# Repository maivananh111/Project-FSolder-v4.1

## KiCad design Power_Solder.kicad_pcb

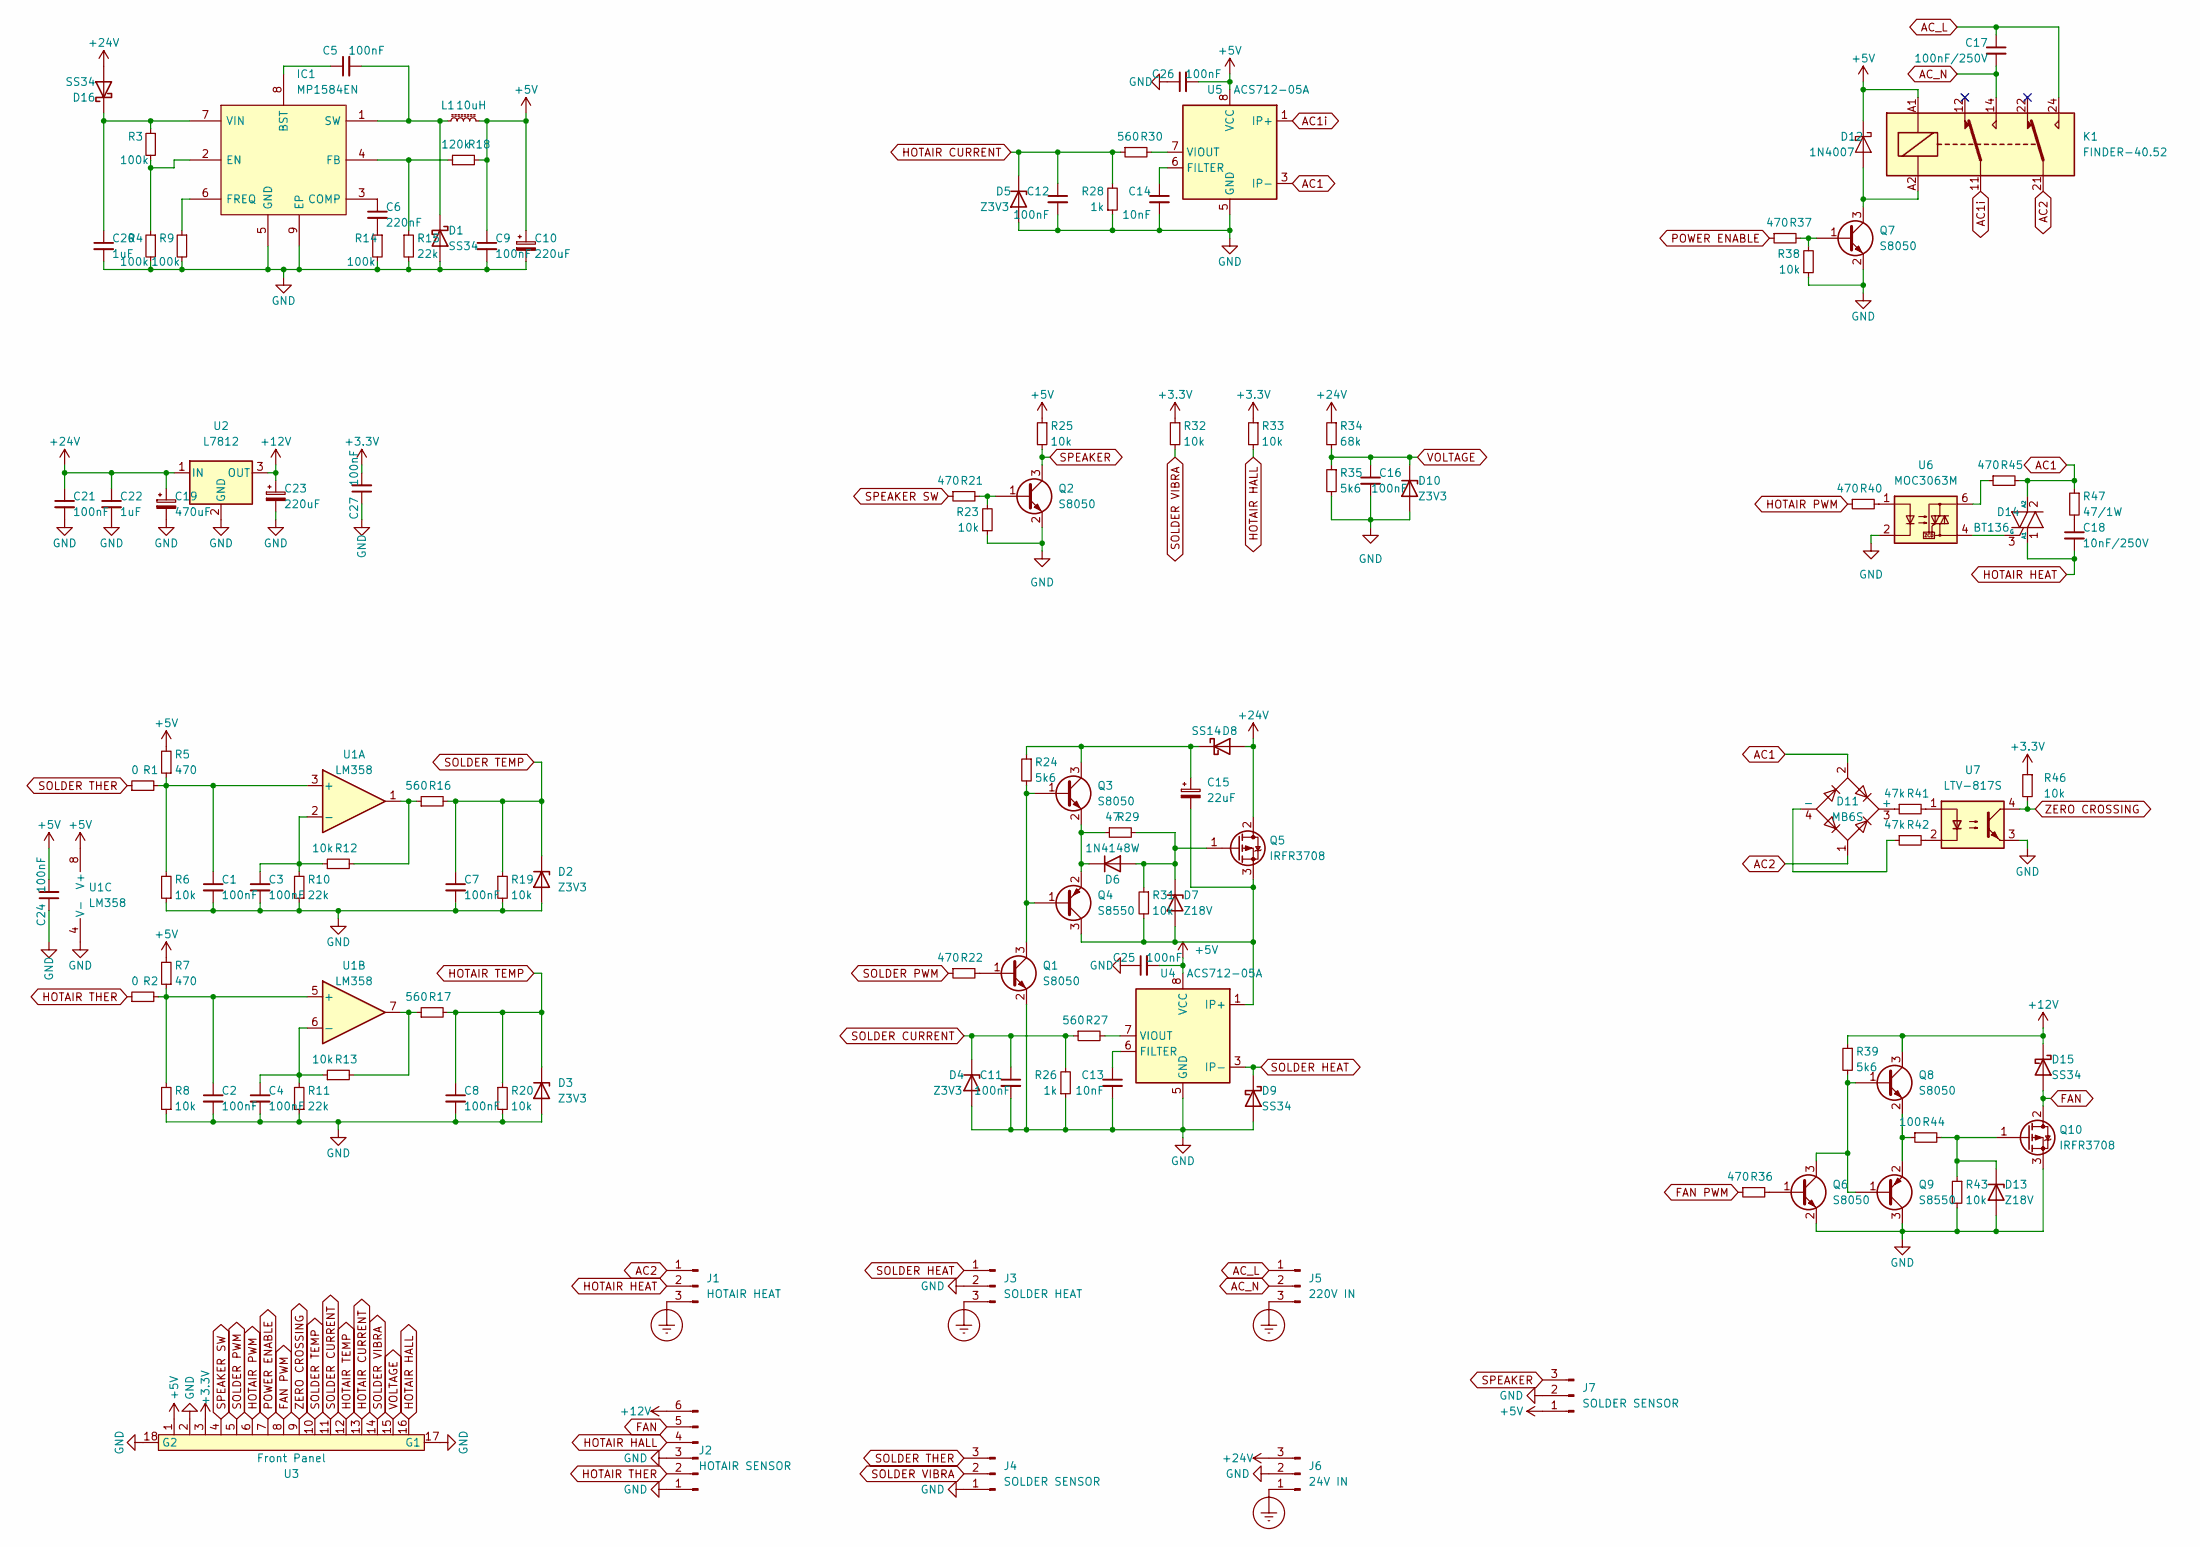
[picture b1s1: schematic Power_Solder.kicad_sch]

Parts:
C1, C2, C3, C4, C5, C7, C8, C9, C11, C12, C16, C21, C24, C25, C26, C27: 100nF; C_0603_1608Metric
C6: 220nF; C_0603_1608Metric
C10, C23: 220uF; CP_Elec_6.3x7.7
C13, C14: 10nF; C_0603_1608Metric
C15: 22uF; CP_EIA-6032-20_AVX-F
C17: 100nF/250V; C_Rect_L13.0mm_W5.0mm_P10.00mm_FKS3_FKP3_MKS4
C18: 10nF/250V; C_1206_3216Metric
C19: 470uF; CP_Elec_10x10.5
C20, C22: 1uF; C_0603_1608Metric
D1, D9, D15, D16: SS34; D_SMA
D2, D3, D4, D5, D10: Z3V3; D_MiniMELF
D6: 1N4148W; D_SOD-123
D7, D13: Z18V; D_MiniMELF
D8: SS14; D_SMA
D11: MB6S; TO-269AA
D12: 1N4007; D_SOD-123F
D14: BT136; TO-252-2
IC1: MP1584EN; SOIC-8-1EP_3.9x4.9mm_P1.27mm_EP2.514x3.2mm
J1: HOTAIR HEAT; JST_VH_B3P-VH-B_1x03_P3.96mm_Vertical
J2: HOTAIR SENSOR; XH_6P_2.54mm_Vertical
J3: SOLDER HEAT; JST_VH_B3P-VH-B_1x03_P3.96mm_Vertical
J4, J7: SOLDER SENSOR; XH_3P_2.54mm_Vertical
J5: 220V IN; JST_VH_B3P-VH-B_1x03_P3.96mm_Vertical
J6: 24V IN; JST_VH_B3P-VH-B_1x03_P3.96mm_Vertical
K1: FINDER-40.52; Relay_DPDT_Finder_40.52
L1: 10uH; L_Abracon_ASPI-0630LR
Q1, Q2, Q3, Q6, Q7, Q8: S8050; SOT-23
Q4, Q9: S8550; SOT-23
Q5, Q10: IRFR3708; TO-252-2
R1, R2: 0; R_0603_1608Metric
R3, R4, R9, R14: 100k; R_0603_1608Metric
R5, R7, R21, R22, R36, R37, R40, R45: 470; R_0603_1608Metric
R6, R8, R12, R13, R19, R20, R23, R25, R31, R32, R33, R38, R43, R46: 10k; R_0603_1608Metric
R10, R11, R15: 22k; R_0603_1608Metric
R16, R17, R27, R30: 560; R_0603_1608Metric
R18: 120k; R_0603_1608Metric
R24, R35, R39: 5k6; R_0603_1608Metric
R26, R28: 1k; R_0603_1608Metric
R29: 47; R_0603_1608Metric
R34: 68k; R_0603_1608Metric
R41, R42: 47k; R_0603_1608Metric
R44: 100; R_0603_1608Metric
R47: 47/1W; R_1206_3216Metric
U1: LM358; SOIC-8_3.9x4.9mm_P1.27mm
U2: L7812; TO-263-3_TabPin2
U3: Front Panel; FPC_16P_1mm
U4, U5: ACS712-05A; SOIC-8_3.9x4.9mm_P1.27mm
U6: MOC3063M; DIP-6_W7.62mm_LongPads
U7: LTV-817S; SMDIP-4_W9.53mm

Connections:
+3.3V: C27.2, R32.1, R33.1, R46.1, U3.3
+5V: C9.1, C10.1, C24.2, C25.2, C26.2, D12.1 (K), J7.1, K1.A1, L1.2, R5.2, R7.2, R18.2, R25.1, U1.8 (V+), U3.1, U4.8 (VCC), U5.8 (VCC)
+12V: C23.1, D15.1 (K), J2.6, Q8.3 (C), R39.1, U2.3 (OUT)
+24V: C19.1, C21.1, C22.1, D8.2 (A), D16.2 (A), J6.3, Q5.2 (D), R34.1, U2.1 (IN)
AC1: D11.2, D14.2 (A2), R45.2, R47.1, U5.3 (IP-), U5.4 (IP-)
AC1i: K1.11, U5.1 (IP+), U5.2 (IP+)
AC2: D11.1, J1.1, K1.21
AC_L: C17.1, J5.1, K1.24
AC_N: C17.2, J5.2, K1.14
Earth_Protective: J1.3, J3.3, J5.3, J6.1
FAN: D15.2 (A), J2.5, Q10.2 (D)
FAN PWM: R36.1, U3.8
GND: C1.2, C2.2, C3.2, C4.2, C7.2, C8.2, C9.2, C10.2, C11.2, C12.2, C13.2, C14.2, C16.2, C19.2, C20.2, C21.2, C22.2, C23.2, C24.1, C25.1, C26.1, C27.1, D1.2 (A), D2.2 (A), D3.2 (A), D4.2 (A), D5.2 (A), D9.2 (A), D10.2 (A), D13.2 (A), IC1.5 (GND), IC1.9 (EP), J2.1, J2.3, J3.2, J4.1, J6.2, J7.2, Q1.2 (E), Q2.2 (E), Q6.2 (E), Q7.2 (E), Q9.3 (C), Q10.3 (S), R4.2, R6.1, R8.1, R9.2, R10.1, R11.1, R14.2, R15.2, R19.2, R20.2, R23.1, R26.1, R28.1, R35.2, R38.1, R43.2, U1.4 (V-), U2.2 (GND), U3.2, U3.17 (G1), U3.18 (G2), U4.5 (GND), U5.5 (GND), U6.2, U7.3
HOTAIR CURRENT: C12.1, D5.1 (K), R28.2, R30.1, U3.13
HOTAIR HALL: J2.4, R33.2, U3.16
HOTAIR HEAT: C18.2, D14.1 (A1), J1.2
HOTAIR PWM: R40.1, U3.6
HOTAIR TEMP: C8.1, D3.1 (K), R17.2, R20.1, U3.12
HOTAIR THER: J2.2, R2.1
unnamed: C6.2, R14.1
unnamed: C18.1, R47.2
unnamed: C5.2, D1.1 (K), IC1.1 (SW), L1.1
unnamed: D6.2 (A), D7.1 (K), Q5.1 (G), R29.2, R31.1
unnamed: D6.1 (K), Q3.2 (E), Q4.2 (E), R29.1
unnamed: C15.2, D7.2 (A), Q4.3 (C), Q5.3 (S), R31.2, U4.1 (IP+), U4.2 (IP+)
unnamed: C15.1, D8.1 (K), Q3.3 (C), R24.1
unnamed: D11.3 (+), R41.1
unnamed: D11.4 (-), R42.1
unnamed: D12.2 (A), K1.A2, Q7.3 (C)
unnamed: D13.1 (K), Q10.1 (G), R43.1, R44.2
unnamed: D14.3 (G), U6.4
unnamed: C20.1, D16.1 (K), IC1.7 (VIN), R3.1
unnamed: C5.1, IC1.8 (BST)
unnamed: C6.1, IC1.3 (COMP)
unnamed: IC1.2 (EN), R3.2, R4.1
unnamed: IC1.4 (FB), R15.1, R18.1
unnamed: IC1.6 (FREQ), R9.1
unnamed: Q1.1 (B), R22.2
unnamed: Q1.3 (C), Q3.1 (B), Q4.1 (B), R24.2
unnamed: Q2.1 (B), R21.2, R23.2
unnamed: Q6.1 (B), R36.2
unnamed: Q6.3 (C), Q8.1 (B), Q9.1 (B), R39.2
unnamed: Q7.1 (B), R37.2, R38.2
unnamed: Q8.2 (E), Q9.2 (E), R44.1
unnamed: R12.2, R16.1, U1.1
unnamed: R13.2, R17.1, U1.7
unnamed: R40.2, U6.1
unnamed: R41.2, U7.1
unnamed: R42.2, U7.2
unnamed: R45.1, U6.6
unnamed: C1.1, R1.2, R5.1, R6.2, U1.3 (+)
unnamed: C3.1, R10.2, R12.1, U1.2 (-)
unnamed: C2.1, R2.2, R7.1, R8.2, U1.5 (+)
unnamed: C4.1, R11.2, R13.1, U1.6 (-)
unnamed: C13.1, U4.6 (FILTER)
unnamed: R27.2, U4.7 (VIOUT)
unnamed: C14.1, U5.6 (FILTER)
unnamed: R30.2, U5.7 (VIOUT)
POWER ENABLE: R37.1, U3.7
SOLDER CURRENT: C11.1, D4.1 (K), R26.2, R27.1, U3.11
SOLDER HEAT: D9.1 (K), J3.1, U4.3 (IP-), U4.4 (IP-)
SOLDER PWM: R22.1, U3.5
SOLDER TEMP: C7.1, D2.1 (K), R16.2, R19.1, U3.10
SOLDER THER: J4.3, R1.1
SOLDER VIBRA: J4.2, R32.2, U3.14
SPEAKER: J7.3, Q2.3 (C), R25.2
SPEAKER SW: R21.1, U3.4
VOLTAGE: C16.1, D10.1 (K), R34.2, R35.1, U3.15
ZERO CROSSING: R46.2, U3.9, U7.4

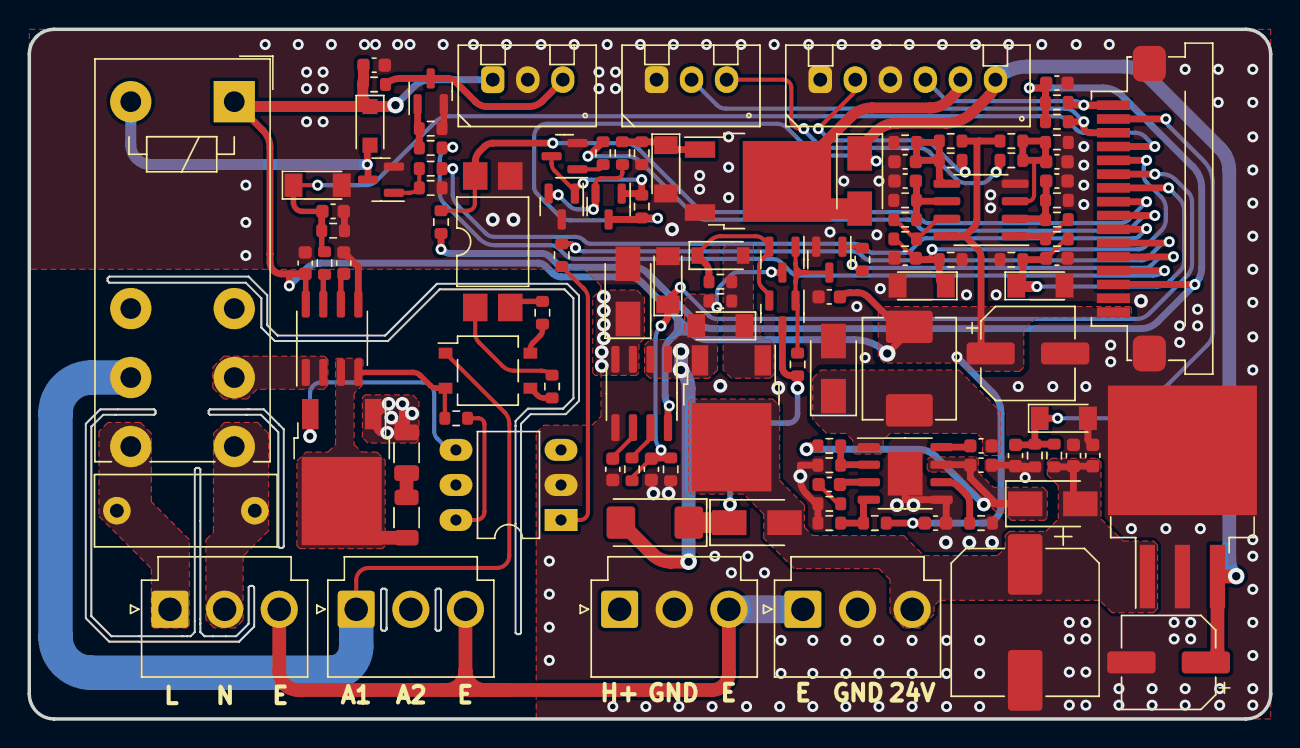
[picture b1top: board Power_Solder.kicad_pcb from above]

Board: 2 copper layers, 90.0 x 50.0 mm, 118 parts (1 on the bottom side), 69 nets.

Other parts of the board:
 : LOGO; MVA_Bmpx20

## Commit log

2023-05-10 tested LCD, Encoder, PWM.
2023-05-15 Some GUI Menu.
2023-05-16 Finish gui main activite.
2023-05-16 add storage features, menu layer 2.
2023-05-18 Final.
2023-08-27 First time add files.
